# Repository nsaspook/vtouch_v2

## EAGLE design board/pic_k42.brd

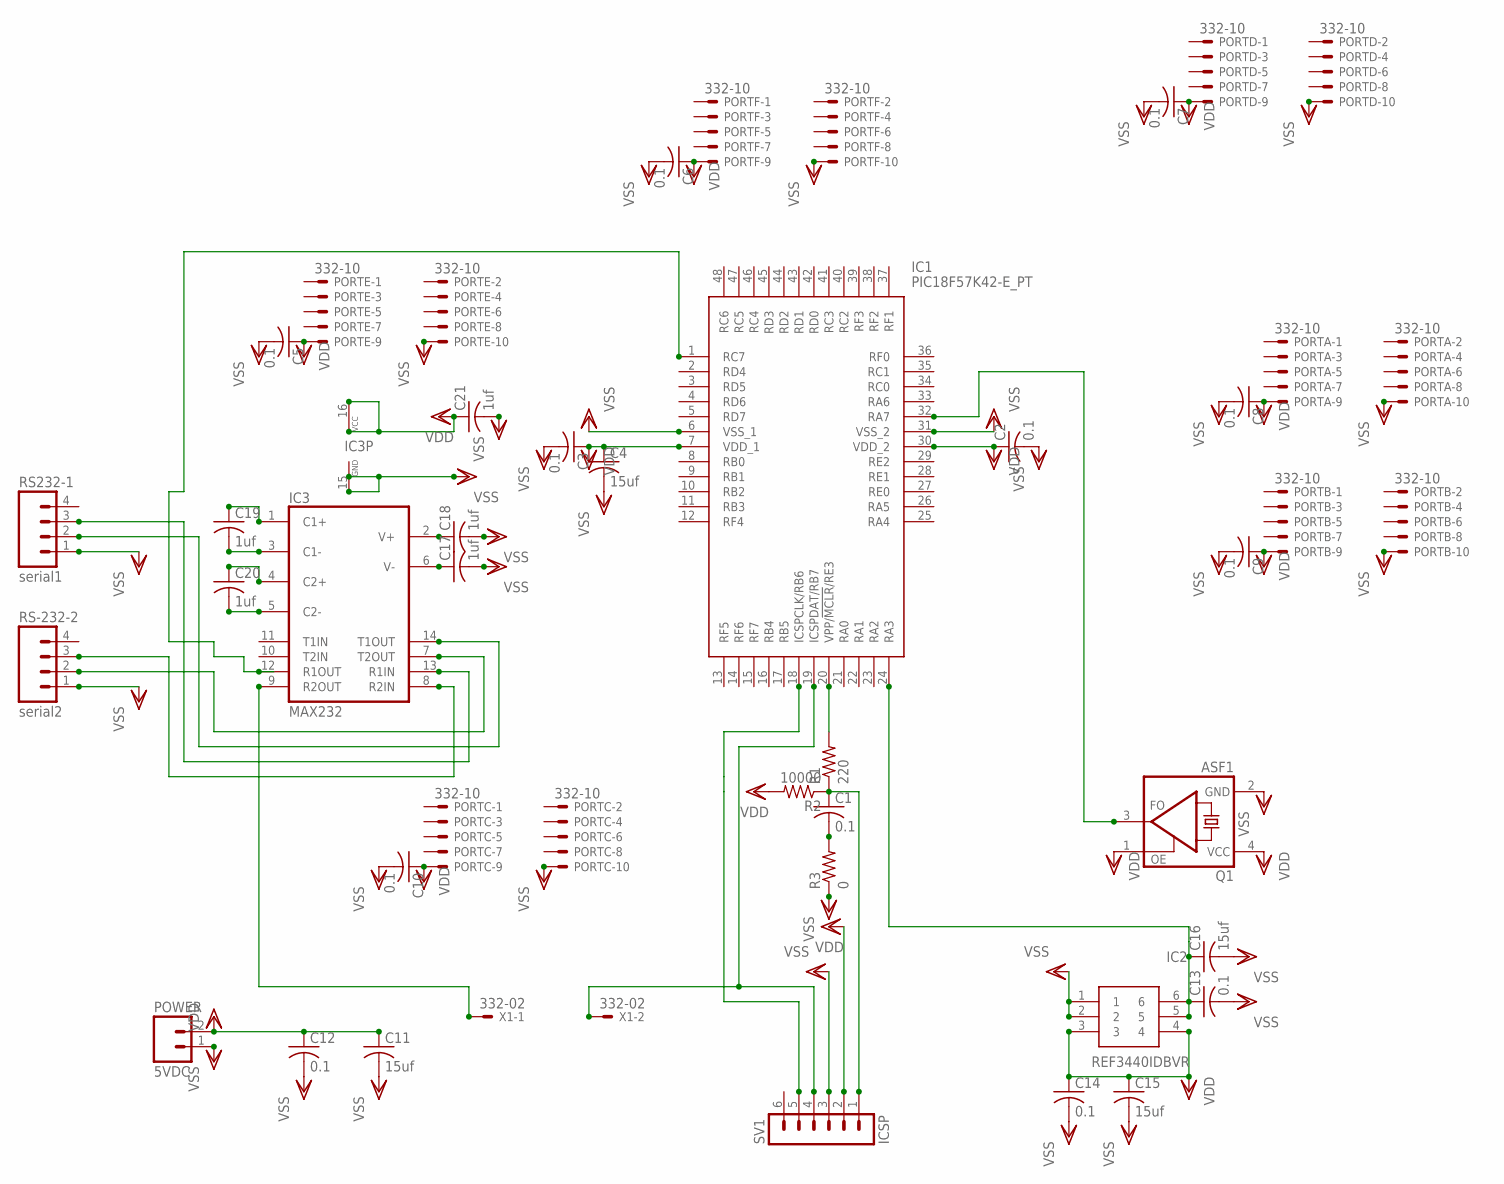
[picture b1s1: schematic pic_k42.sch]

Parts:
C1, C2, C3, C5, C6, C7, C8, C9, C10, C12, C13, C14: 0.1; C1206
C4, C11, C15, C16: 15uf; C1206
C17, C18, C19, C20, C21: 1uf; C0805
IC1: PIC18F57K42-E_PT; QFP50P900X900X120-48N
IC2: REF3440IDBVR; SOP95P280X145-6N
IC3: MAX232; DIL16
PORTA: 332-10
PORTB: 332-10
PORTC: 332-10
PORTD: 332-10
PORTE: 332-10
PORTF: 332-10
POWER: 5VDC; 02P
Q1: ASF1; ASF
R1: 220; R1206
R2: 10000; R1206
R3: 0; R1206
RS232-1: serial1; 04P
RS-232-2: serial2; 04P
SV1: ICSP; MA06-1
X1: 332-02

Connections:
unnamed 0: C1.1, R1.1, R2.1, SV1.1; also elsewhere on the board
unnamed: IC1.20 (VPP/!MCLR!/RE3), R1.2
unnamed: C1.2, R3.2
unnamed: IC1.32 (RA7), Q1.3 (FO)
unnamed: C17.1, IC3.6 (V-)
unnamed: IC1.19 (ICSPDAT/RB7), SV1.4, X1.2
unnamed 6: IC1.18 (ICSPCLK/RB6), SV1.5; also elsewhere on the board
unnamed: C13.1, C16.1, IC1.24 (RA3), IC2.5, IC2.6
unnamed: C18.1, IC3.2 (V+)
unnamed: C19.1, IC3.1 (C1+)
unnamed: C20.1, IC3.4 (C2+)
unnamed: C20.2, IC3.5 (C2-)
unnamed: C19.2, IC3.3 (C1-)
unnamed: IC3.14 (T1OUT), RS232-1.2
unnamed: IC3.7 (T2OUT), RS-232-2.2
unnamed: IC3.13 (R1IN), RS232-1.3
unnamed: IC3.8 (R2IN), RS-232-2.3
unnamed: IC1.1 (RC7), IC3.12 (R1OUT)
unnamed: IC3.9 (R2OUT), X1.1
unnamed: IC1.48 (RC6), IC3.11 (T1IN)
unnamed 21: IC3.10 (T2IN); also elsewhere on the board
unnamed 22: IC1.27 (RE0); also elsewhere on the board
unnamed 23: IC1.28 (RE1); also elsewhere on the board
unnamed 24: IC1.29 (RE2); also elsewhere on the board
VDD: C2.1, C3.1, C4.1, C5.1, C6.1, C7.1, C8.1, C9.1, C10.1, C11.1, C12.1, C14.1, C15.1, C21.1, IC1.7 (VDD_1), IC1.30 (VDD_2), IC2.3, IC2.4, IC3.16 (VCC), PORTA.9, PORTB.9, PORTC.9, PORTD.9, PORTE.9, PORTF.9, POWER.2, Q1.1 (OE), Q1.4 (VCC), R2.2, SV1.2
VSS: C2.2, C3.2, C4.2, C5.2, C6.2, C7.2, C8.2, C9.2, C10.2, C11.2, C12.2, C13.2, C14.2, C15.2, C16.2, C17.2, C18.2, C21.2, IC1.6 (VSS_1), IC1.31 (VSS_2), IC2.1, IC2.2, IC3.15 (GND), PORTA.10, PORTB.10, PORTC.10, PORTD.10, PORTE.10, PORTF.10, POWER.1, Q1.2 (GND), R3.1, RS232-1.1, RS-232-2.1, SV1.3; also elsewhere on the board

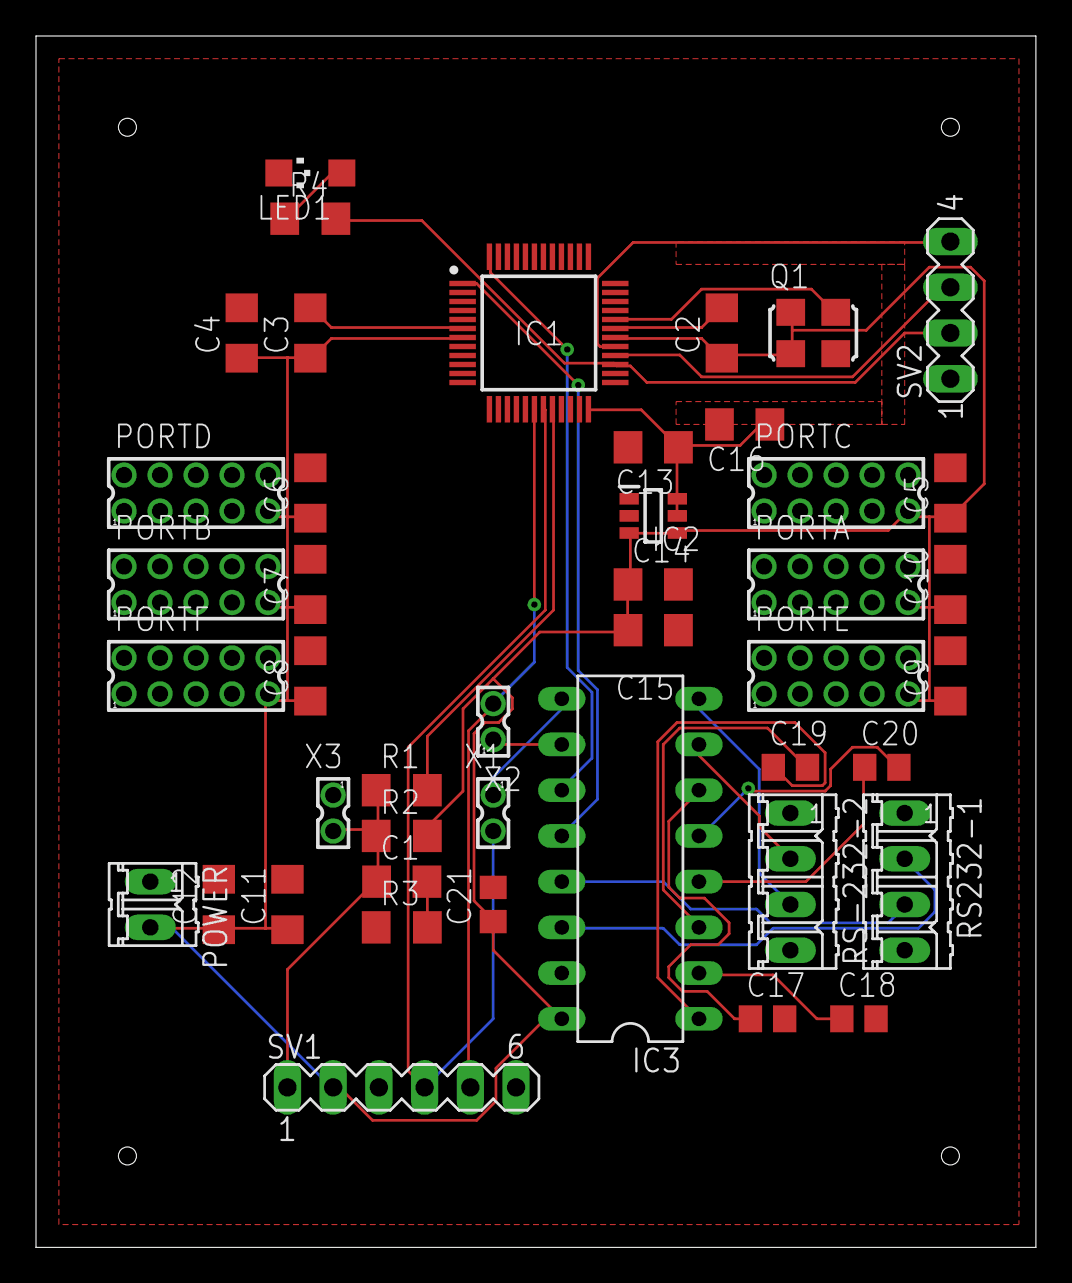
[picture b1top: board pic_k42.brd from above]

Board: 2 copper layers, 55.6 x 67.3 mm, 44 parts (0 on the bottom side), 27 nets.

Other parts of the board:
LED1: RUN; CHIPLED_1206
R4: 220; R1206
SV2: DEBUG; MA04-1
X2, X3: 332-02

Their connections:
unnamed 0: X3.2; also elsewhere on the board
unnamed 6: X2.2; also elsewhere on the board
unnamed: LED1.A, R4.1
unnamed 21: X2.1; also elsewhere on the board
unnamed 22: R4.2, SV2.2; also elsewhere on the board
unnamed 23: SV2.3; also elsewhere on the board
unnamed 24: SV2.4; also elsewhere on the board
VSS: LED1.C, SV2.1, X3.1; also elsewhere on the board

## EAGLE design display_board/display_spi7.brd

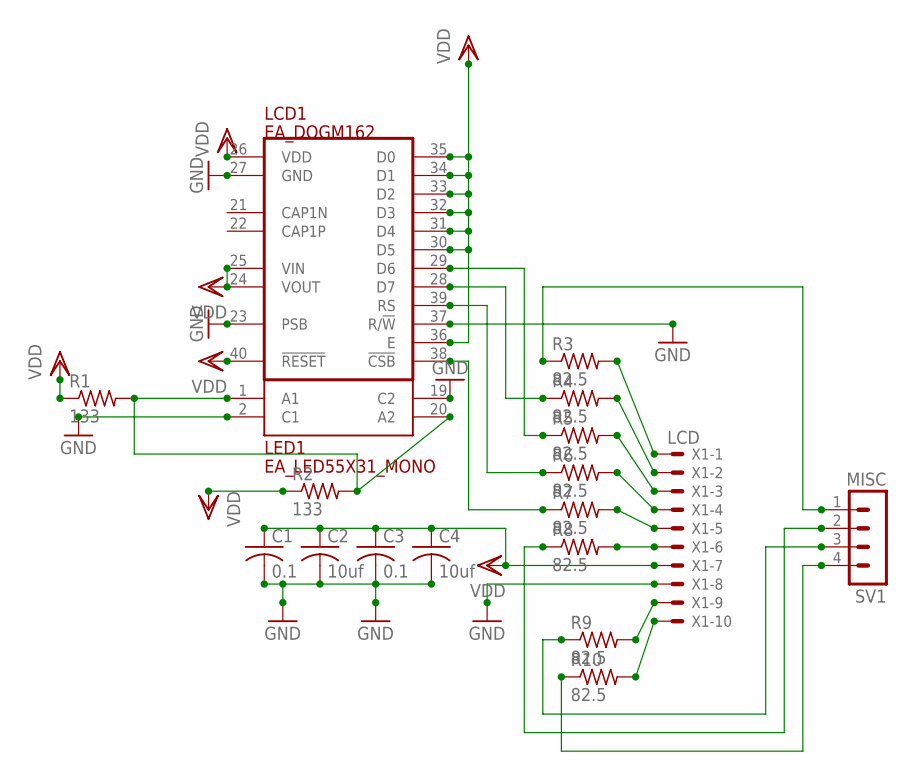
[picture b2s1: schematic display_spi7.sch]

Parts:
C1, C3: 0.1; C1206
C2, C4: 10uf; C1206
LCD1: EA_DOGM162; EA_DOGM
LED1: EA_LED55X31_MONO; EA_LED55X31
R1, R2: 133; R1206
R3, R4, R5, R6, R7, R8, R9, R10: 82.5; R1206
SV1: MISC; MA04-1
X1: LCD; 22-23-2101

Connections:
GND: C1.2, C2.2, C3.2, C4.2, LCD1.23 (PSB), LCD1.27 (GND), LCD1.37 (R/!W!), LED1.2 (C1), LED1.19 (C2), X1.8
unnamed: R3.2, X1.1
unnamed: R4.2, X1.2
unnamed: R5.2, X1.3
unnamed: R6.2, X1.4
unnamed: R7.2, X1.5
unnamed: R8.2, X1.6
unnamed: R9.2, X1.9
unnamed: R10.2, X1.10
unnamed: LCD1.28 (D7), R4.1
unnamed: LCD1.29 (D6), R5.1
unnamed: LCD1.39 (RS), R6.1
unnamed: LCD1.38 (!CSB!), R7.1
unnamed: R3.1, SV1.1
unnamed: R8.1, SV1.2
unnamed: R9.1, SV1.3
unnamed: R10.1, SV1.4
unnamed: LED1.1 (A1), LED1.20 (A2), R1.2, R2.2
VDD: C1.1, C2.1, C3.1, C4.1, LCD1.24 (VOUT), LCD1.25 (VIN), LCD1.26 (VDD), LCD1.30 (D5), LCD1.31 (D4), LCD1.32 (D3), LCD1.33 (D2), LCD1.34 (D1), LCD1.35 (D0), LCD1.36 (E), LCD1.40 (!RESET!), R1.1, R2.1, X1.7

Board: 2 copper layers, 18 parts (0 on the bottom side), 19 nets, no tracks yet.

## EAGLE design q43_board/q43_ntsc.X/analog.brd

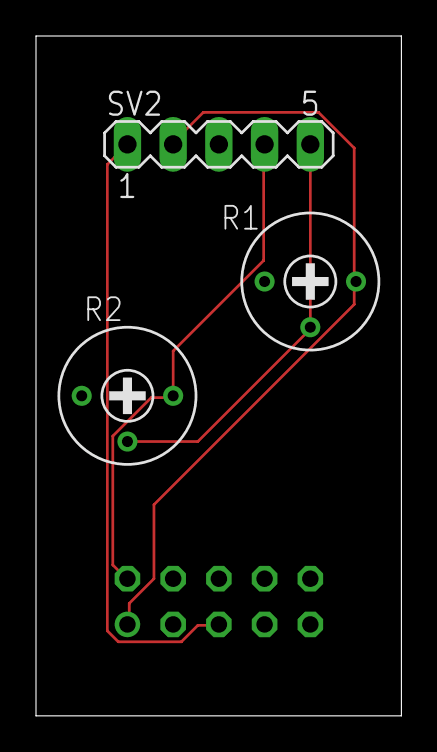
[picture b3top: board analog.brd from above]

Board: 2 copper layers, 20.3 x 37.8 mm, 4 parts (1 on the bottom side), 5 nets.

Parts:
R1: 1k; RTRIM3339P
R2: 1K; RTRIM3339P
SV1: Q43 DIGITAL; FE05-2
SV2: NTSC VIDEO; MA05-1

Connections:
unnamed: R1.3, SV1.1, SV2.2
unnamed: R2.3, SV1.2, SV2.4
unnamed: R1.2, R2.2, SV2.5
unnamed: SV1.5, SV2.1
VSS: R1.1, R2.1, SV1.10, SV2.3

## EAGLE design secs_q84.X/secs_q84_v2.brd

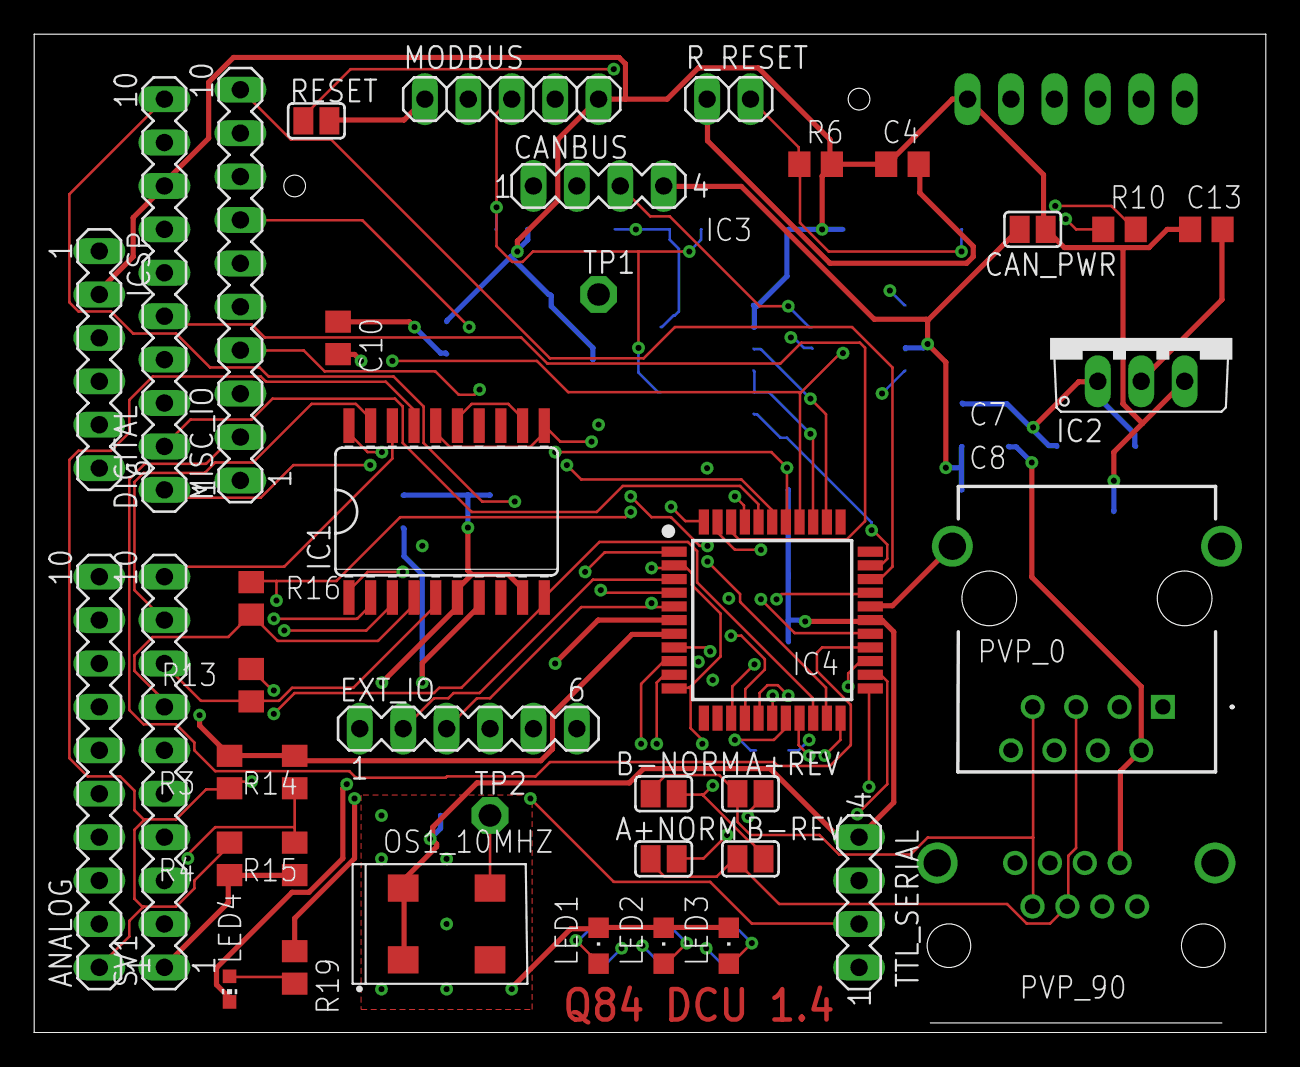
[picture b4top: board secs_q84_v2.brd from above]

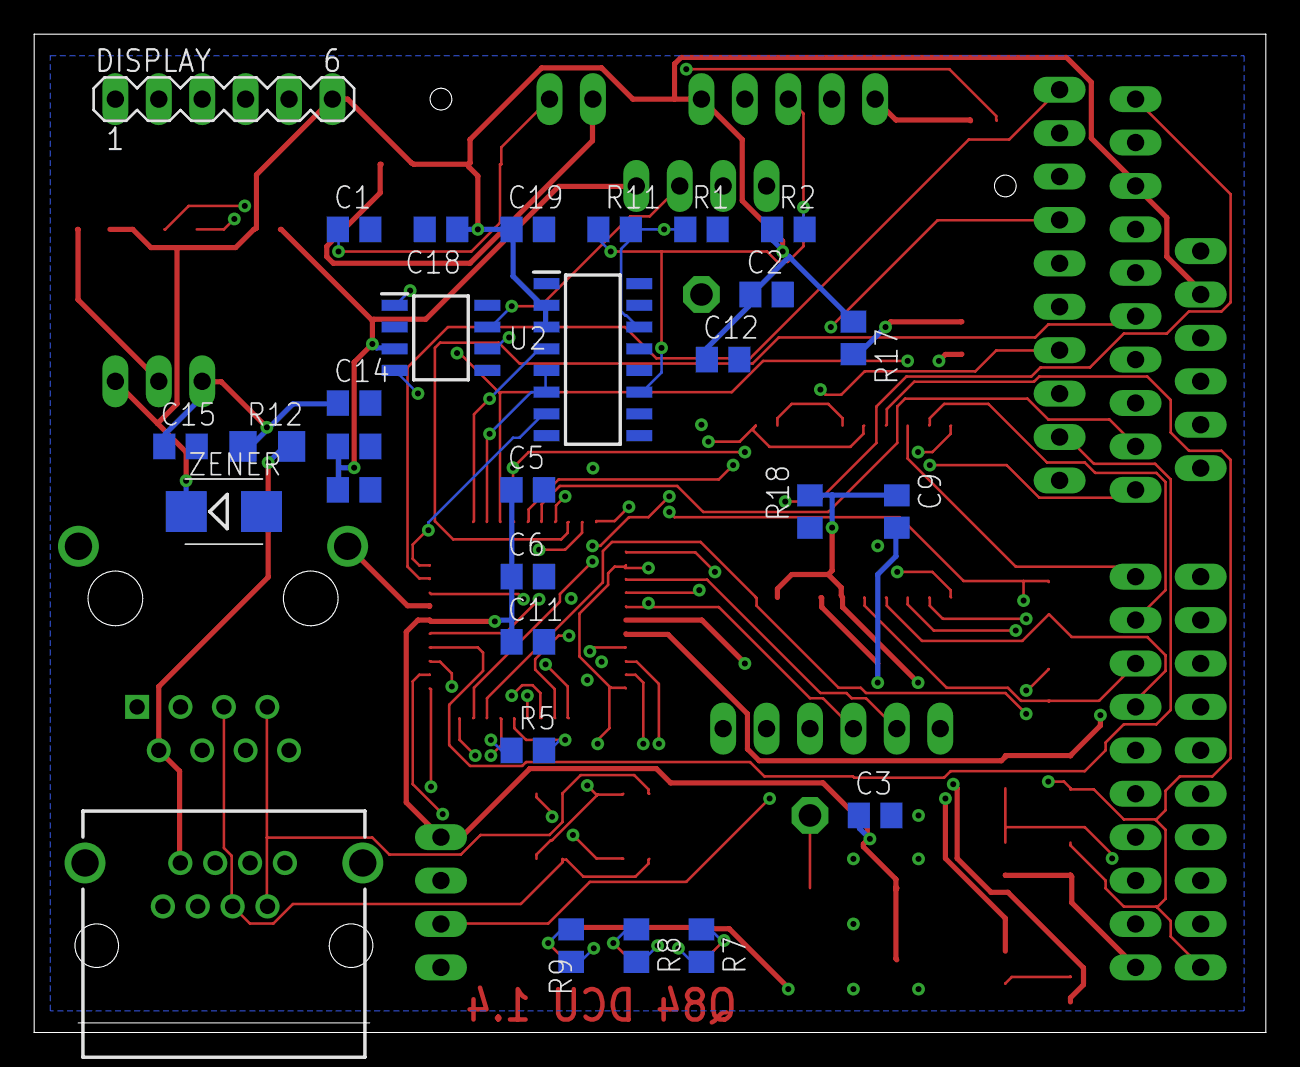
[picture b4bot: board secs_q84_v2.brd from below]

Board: 4 copper layers, 72.1 x 58.4 mm, 68 parts (28 on the bottom side), 58 nets.

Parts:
A+NORM: A+NORM; SJ
A+REV: A+REV; SJ
ANALOG: Analog; MA10-1
B-NORM: B-NORM; SJ
B-REV: B-REV; SJ
C1, C2, C3, C5, C7, C9, C11, C12, C14, C18: 0.1uf; C0805
C4, C6, C8, C10, C13, C15, C19: 10uf; C0805
CANBUS: CANBUS; MA04-1
CAN_PWR: CAN_PWR; SJ
DIGITAL: Digtal; MA10-1
DISPLAY: DISPLAY; MA06-1
EXT_IO: EXT_IO; MA06-1
IC1: MAX203ECWP; SO20L
IC2: 7805TV; TO220V
IC3: ADM3095EBRZ; SOIC127P600X175-16N
IC4: PIC18F47Q84-I_PT; QFP80P1200X1200X120-44N
ICSP: ICSP; MA06-1
LED1: L1; CHIPLED_0805
LED2: L2; CHIPLED_0805
LED3: L3; CHIPLED_0805
LED4: POWER; CHIP-LED0603
MISC_IO: misc-io; MA10-1
MODBUS: MODBUS; 1X05
OS1_10MHZ: OSC-OE-CFPS-72; 7.2X5.2-4-PAD
PVP_0: 3-1734577-4; 317345774
PVP_90: GLX-S-88M
R1, R2: 680; R0805
R3, R4, R14, R15: 12.1k; R0805
R5: 56ohm; R0805
R6: 10k; R0805
R7, R8, R9, R19: 1k; R0805
R10: 120ohm; R0805
R11: 120; R0805
R12: 0 ohm fuse; R1206
R13, R16: 86.6k; R0805
R17, R18: 0ohm; R0805
RESET: reset; SJ
R_RESET: remote_reset; 1X02
SV1: SERIAL BUS; MA10-1
TP1, TP2: PTR1PAD1-13; P1-13
TTL_SERIAL: TTL Serial; MA04-1
U2: TCAN330GDR; SOIC127P600X175-8N
ZENER: 5.6V; SMB

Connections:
AN0: ANALOG.10, IC4.19
AN4: ANALOG.4, IC4.23
AN5: ANALOG.5, IC4.24
CANRX: IC4.8, U2.4
CANTX: IC4.14, U2.1
CAN_N: CANBUS.1, R10.1, U2.6
CAN_P: CANBUS.3, R10.2, U2.7
CAN_VCC: C7.1, C8.1, CANBUS.4, CAN_PWR.1, U2.3
CLOCKO: IC4.31, MISC_IO.10
CPU_CLK: IC4.30, OS1_10MHZ.3, TP2.TP
CS: DIGITAL.3, DISPLAY.1, IC4.41
DB0: DIGITAL.1, IC4.39
DB1: DIGITAL.2, IC4.40
DERE: IC3.5, IC3.6, IC4.36, TP1.TP
DLED: IC4.2, IC4.11, MISC_IO.4, R9.2
GND: C9.2, C10.2, IC1.6, IC1.9, LED4.C, R18.2
MB_A: A+NORM.2, A+REV.2, IC3.11, MODBUS.3, R2.2, R11.1
MB_B: B-NORM.2, B-REV.2, IC3.14, MODBUS.2, R1.1, R11.2
MB_RX: ANALOG.6, IC1.3, IC3.7, IC4.32
MB_TX: ANALOG.7, IC1.2, IC3.4, IC4.35
MCLR_SIG: IC4.18, ICSP.1, MISC_IO.8, R5.2
MISC: IC4.26, MISC_IO.2
MLED: IC4.9, R7.2
unnamed: LED4.A, R19.2
unnamed: LED1.A, R7.1
unnamed: LED2.A, R8.1
unnamed: LED3.A, R9.1
PC_RX2: IC1.20, IC4.38, TTL_SERIAL.3
PC_TX2: IC1.1, IC4.4, TTL_SERIAL.2
PGC: EXT_IO.5, IC4.16, ICSP.5
PGD: EXT_IO.6, IC4.17, ICSP.4
PVP_A: A+NORM.1, B-REV.1, PVP_0.5, PVP_90.5
PVP_B: A+REV.1, B-NORM.1, PVP_0.7, PVP_90.7
RB5: EXT_IO.4, IC4.15, MISC_IO.6
RD5: EXT_IO.2, IC4.3, MISC_IO.5
RD7: EXT_IO.3, IC4.5, MISC_IO.7
RE2: IC4.27, MISC_IO.3
RELAY: IC4.25, MISC_IO.1
RLED: IC4.10, R8.2
RS232EQRX: IC1.19, SV1.9
RS232EQTX: IC1.18, SV1.10
RS232RX: IC1.4, R16.2, SV1.7
RS232TX: IC1.5, R13.1, SV1.8
RSJ1: ANALOG.1, IC1.10, IC1.17, IC4.20, R3.1, R4.2, R13.2
RSJ2: IC1.12, IC1.15
RSJ3: ANALOG.2, IC1.11, IC1.16, IC4.21, R14.2, R15.1, R16.1
R_RESET: C1.1, R5.1, R6.1, RESET.1, R_RESET.2
SCK1: DIGITAL.4, DISPLAY.3, IC4.37
SDI1: DIGITAL.5, IC4.42
SDO1: DIGITAL.6, DISPLAY.4, IC4.43
UC_RX: DIGITAL.10, IC4.1
UC_TX: DIGITAL.7, IC4.44
V+: PVP_0.2, PVP_90.2, R12.2
V+BUS: C14.1, C15.1, IC2.1, R12.1
VCC: C9.1, C10.1, IC1.7, R17.2, R19.1
VDD: ANALOG.8, C2.1, C3.1, C4.1, C5.1, C6.1, C11.1, C12.1, C13.1, C18.1, C19.1, CAN_PWR.2, DIGITAL.8, DISPLAY.6, IC2.3, IC3.2, IC3.3, IC4.7, IC4.28, ICSP.2, MODBUS.5, OS1_10MHZ.1, OS1_10MHZ.4, R2.1, R3.2, R6.2, R14.1, R17.1, TTL_SERIAL.4, ZENER.C
VREF: ANALOG.3, IC4.22
VSS: ANALOG.9, C1.2, C2.2, C3.2, C4.2, C5.2, C6.2, C7.2, C8.2, C11.2, C12.2, C13.2, C14.2, C15.2, C18.2, C19.2, CANBUS.2, DIGITAL.9, DISPLAY.5, EXT_IO.1, IC2.2, IC3.1, IC3.8, IC3.9, IC3.10, IC3.12, IC3.13, IC3.15, IC3.16, IC4.6, IC4.29, ICSP.3, LED1.C, LED2.C, LED3.C, MISC_IO.9, MODBUS.1, MODBUS.4, OS1_10MHZ.2, PVP_0.6, PVP_0.9, PVP_0.10, PVP_90.6, PVP_90.S1, PVP_90.S2, R1.2, R4.1, R15.2, R18.1, RESET.2, R_RESET.1, SV1.1, SV1.6, TTL_SERIAL.1, U2.2, U2.5, U2.8, ZENER.A

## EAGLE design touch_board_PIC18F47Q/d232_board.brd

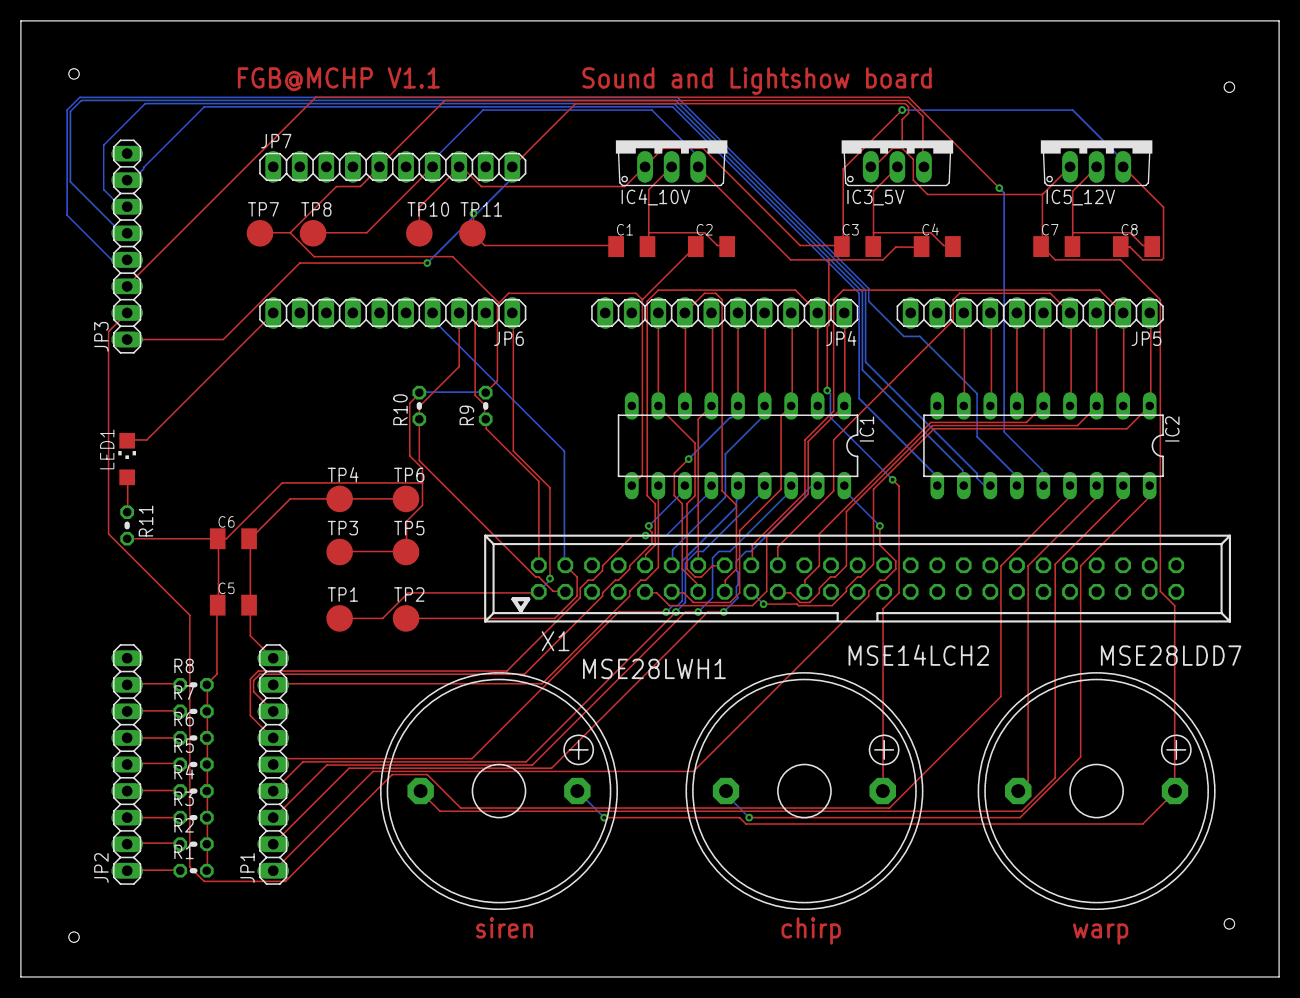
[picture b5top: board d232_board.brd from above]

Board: 2 copper layers, 120.3 x 91.4 mm, 46 parts (0 on the bottom side), 51 nets.

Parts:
C1, C3, C6, C7: 0.47; C1206K
C2, C4, C5, C8: 22uf; C1206K
IC1, IC2: uln2803; DIL18
IC3_5V, IC4_10V, IC5_12V: 7805TV; TO220V
JP1: LEDC; 1X09
JP2: LEDP; 1X09
JP3: PORTIO; 1X08
JP4: PORT2; 1X10
JP5: PORT3; 1X10
JP6: PORT1; 1X10
JP7: DC POWER; 1X10
LED1: PWR; CHIPLED_1206
MSE14LCH2, MSE28LDD7, MSE28LWH1: EB2209A
R1, R2, R3, R4, R5, R6, R7, R8, R9, R10: 91; 0204V
R11: 1k; 0204V
TP1, TP2, TP3, TP4, TP5, TP6, TP7, TP8, TP10, TP11: TPB2,54; B2,54
X1: 057-050-1

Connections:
+5V: C2.1, C5.1, C6.1, IC1.10, IC3_5V.3, JP7.5, R1.2, R2.2, R3.2, R4.2, R5.2, R6.2, R7.2, R8.2, R9.2, R10.2, R11.2, TP3.TP, TP5.TP, TP7.TP
+10V: C4.1, IC4_10V.3, JP7.7, MSE14LCH2.+, TP8.TP
+12V: C3.1, C8.1, IC4_10V.1, IC5_12V.3, JP7.8, TP10.TP
+24V: C1.1, C7.1, IC3_5V.1, IC5_12V.1, JP3.1, JP7.10, MSE28LDD7.+, MSE28LWH1.+, TP11.TP
GND: C1.2, C2.2, C3.2, C4.2, C5.2, C6.2, C7.2, C8.2, IC1.9, IC2.9, IC3_5V.2, IC4_10V.2, IC5_12V.2, JP1.9, JP2.9, JP3.8, JP4.10, JP5.10, JP6.10, JP7.1, JP7.2, JP7.3, JP7.4, LED1.C, TP4.TP, TP6.TP, X1.50
unnamed: IC1.18, JP1.1
unnamed: IC1.17, JP1.2
unnamed: IC1.16, JP1.3
unnamed: IC1.15, JP1.4
unnamed: IC1.14, JP1.5
unnamed: IC1.13, JP1.6
unnamed: IC1.12, JP1.7
unnamed: IC1.11, JP1.8
unnamed: IC1.1, JP4.1, X1.9
unnamed: IC1.2, JP4.2, X1.10
unnamed: IC1.3, JP4.3, X1.11
unnamed: IC1.4, JP4.4, X1.12
unnamed: IC1.5, JP4.5, X1.13
unnamed: IC1.6, JP4.6, X1.14
unnamed: IC1.7, JP4.7, X1.15
unnamed: IC1.8, JP4.8, X1.16
unnamed: IC2.1, JP5.1, X1.17
unnamed: IC2.2, JP5.2, X1.18
unnamed: IC2.3, JP5.3, X1.19
unnamed: IC2.4, JP5.4, X1.20
unnamed: IC2.5, JP5.5, X1.21
unnamed: IC2.6, JP5.6
unnamed: IC2.7, JP5.7
unnamed: IC2.8, JP5.8
unnamed: IC2.18, MSE14LCH2.-
unnamed: IC2.17, MSE28LWH1.-
unnamed: IC2.16, MSE28LDD7.-
unnamed: JP6.1, TP1.TP, X1.1
unnamed: JP6.2, R9.1, X1.2
unnamed: JP6.3, R10.1, X1.3
unnamed: JP6.4, TP2.TP, X1.4
unnamed: JP2.1, R1.1
unnamed: JP2.2, R2.1
unnamed: JP2.3, R3.1
unnamed: JP2.4, R4.1
unnamed: JP2.5, R5.1
unnamed: JP2.6, R6.1
unnamed: JP2.7, R7.1
unnamed: JP2.8, R8.1
unnamed: IC2.15, JP3.2
unnamed: IC2.14, JP3.3
unnamed: IC2.13, JP3.4
unnamed: IC2.12, JP3.5
unnamed: IC2.11, JP3.6
unnamed: IC2.10, JP3.7
unnamed: LED1.A, R11.1
